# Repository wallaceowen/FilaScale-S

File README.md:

# FilaScale-S
Simple through-hole board implementing a no-gui FilaScale

This is a small Arduino Nano-based board designed to implement the sensor suite of a FilaScale
but without a GUI, and using through-hole parts.

It was built to the requirements of a filament monitoring device.  The board provides:

* Humidity, temperature and weight monitoring of a spool of filament in a drybox
* RFID tag reader
* Serial communications with a host over USB

## The board (KiCAD rendering)

## The code
The Code is at https://github.com/wallaceowen/FilaScale/tree/nogui_nano

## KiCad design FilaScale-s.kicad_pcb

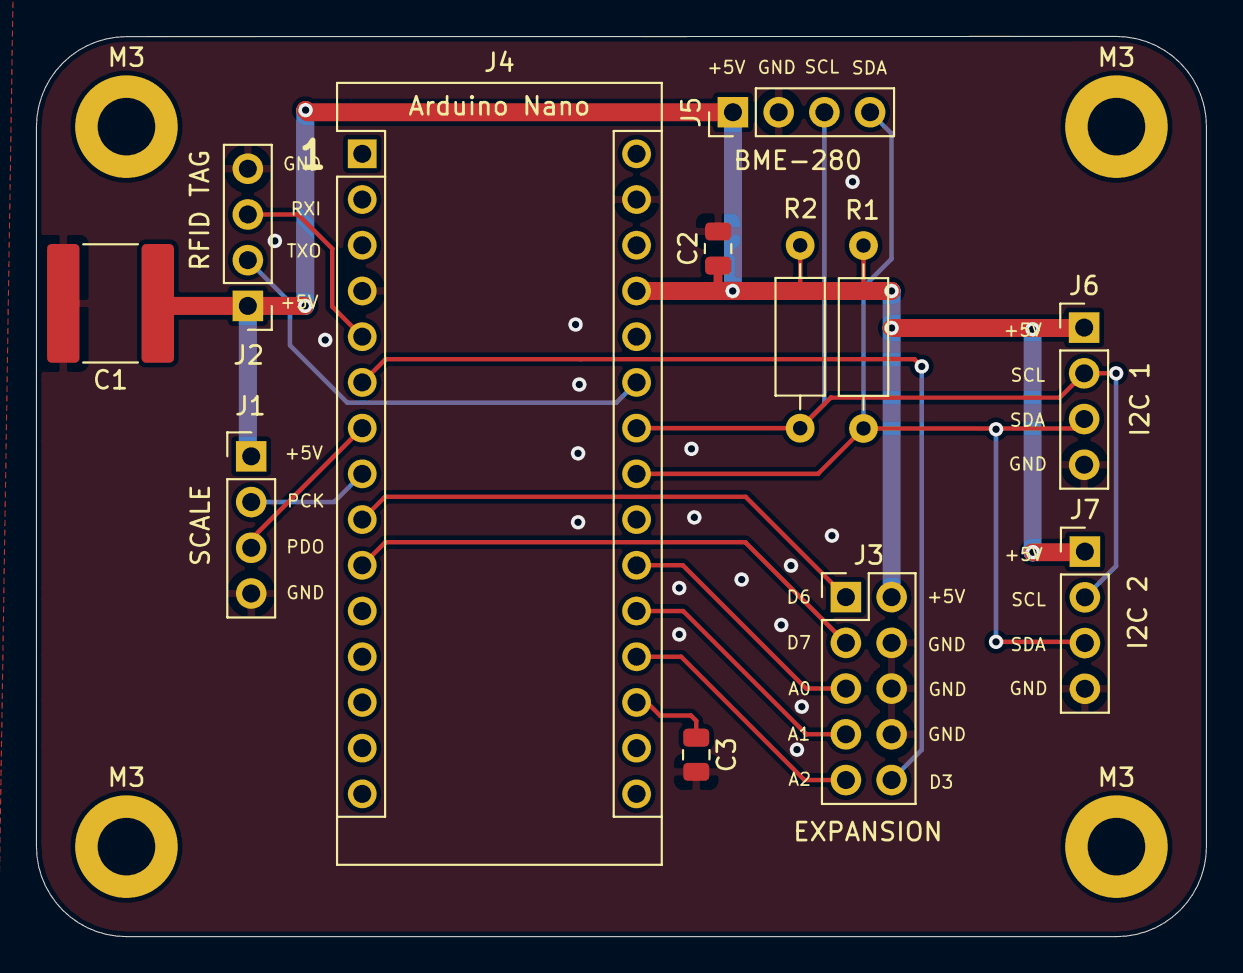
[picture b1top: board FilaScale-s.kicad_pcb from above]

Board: 2 copper layers, 65.0 x 50.0 mm, 16 parts (0 on the bottom side), 15 nets.

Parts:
C1: 10uF; C_2225_5664Metric_Pad1.80x6.60mm_HandSolder
C2, C3: .1uF; C_0805_2012Metric
J1: HX711MOD; PinHeader_1x04_P2.54mm_Vertical
J2: RFID; PinHeader_1x04_P2.54mm_Vertical
J3: EXP1; PinHeader_2x05_P2.54mm_Vertical
J4: Arduino_Nano_v3.x; Arduino_Nano
J5: BME-280; PinHeader_1x04_P2.54mm_Vertical
J6: I2C 1; PinHeader_1x04_P2.54mm_Vertical
J7: I2C 2; PinHeader_1x04_P2.54mm_Vertical
M3, M3#2, M3#3, M3#4: MountingHole_3.2mm_M3_ISO7380_Pad
R1, R2: 3.9K; R_Axial_DIN0207_L6.3mm_D2.5mm_P10.16mm_Horizontal

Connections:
+5V: C1.1, C2.1, J1.1, J2.1, J3.2, J4.27, J5.1, J6.1, J7.1, R1.1, R2.2
/A0: J3.9, J4.19
/A1: J3.7, J4.20
/A2: J3.5, J4.21
/AREF: C3.1, J4.18
/D3: J3.10, J4.6
/D6: J3.1, J4.9
/D7: J3.3, J4.10
/PD_DOUT: J1.3, J4.7
/PD_SCK: J1.2, J4.8
/RFID_RXI: J2.3, J4.5
/RFID_TXO: J2.2, J4.25
/SCL: J4.24, J5.3, J6.2, J7.2, R2.1
/SDA: J4.23, J5.4, J6.3, J7.3, R1.2
GND: C1.2, C2.2, C3.2, J1.4, J2.4, J3.4, J3.6, J3.8, J4.4, J4.29, J5.2, J6.4, J7.4

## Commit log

2021-10-05 Put the files in
2021-10-05 Add picture of rendered board
2021-10-06 Rounded the corners, made it 50x50mm in size Added a couple of entries to .gitignore
2021-10-11 Add expansion connectors for things I can't forsee but users might want available
2021-10-14 Fix label on front silkscreen;
2021-11-28 Cleanup, add bypass and decoupling caps, add expansion port
2021-11-28 Add a jpg of the 3D render of the board
2021-11-28 Fix silkscreen
2021-11-28 Update README.md
    Updated model
2021-12-18 Change layout to accommodate horizontal connectors, to miminize height
